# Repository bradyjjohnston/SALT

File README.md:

# 🍞 SALT - Slice And Loaf Telemetry

> A modular home automation and environmental sensing platform, developed in collaboration with **EE4737** and the open-source [BREAD] project.

---

## Overview

BREAD is a modular embedded systems architecture built around a central **Loaf** board and hot-swappable **Slice** modules. Each slice handles its own sensing or control functionality and communicates back to the loaf over a shared protocol (UART). Together, they form a capable at-home weather station and automation hub.

---

## Architecture

```
┌────────────────────────────────────────┐
│              Loaf (Main Board)         │
│   Central controller with female conn. │
│   handles aggregation, data, and logic │
└────────┬────────┬────────┬─────────────┘
         │        │        │
    ┌────┴──┐ ┌───┴──┐ ┌───┴──┐
    │Slice 1│ │Slice2│ │Slice3│  ...
    │SENSE  │ │ ACT. │ │ OPT. │
    └───────┘ └──────┘ └──────┘
```

- **Loaf** — the main board with female connectors, acts as the central hub
- **Slices** — individual modules that plug into the loaf via edge connectors and expose sensor data or control outputs over UART/I2C

---

## Features

- 🌡️ **Environmental monitoring** — temperature, humidity, pressure (BME280)
- 🌐 **Weather data integration** — pulls external weather API data
- 📡 **Modular slice communication** — UART packet protocol between slices and loaf
- 🔌 **Plug-and-play expansion** — add new slices without redesigning the core system
- 🏠 **Home automation ready** — designed to grow into broader automation use cases

---

## Hardware

| Component | Role |
|-----------|------|
| LOAF | facilitates slice data |
| Sense Slice | temp / humidity / pressure sensor / boot sensor |
| Actuation Slice | salt distribution motor control |
| Optics Slice | camera processing and control |
| Power Slice | power outage detection and power distribution |

---

## Communication Protocol

Slices send formatted UART packets to the loaf via DMA when requested by the master MCU. Each packet includes:

- Formatted sensor data

---

## Getting Started

> ⚠️ Hardware required. Software setup instructions coming soon.

1. Clone this repo
2. Open in **STM32CubeIDE**
3. Flash the slice firmware to your Nucleo F303K8
4. Connect the slice to the loaf board via the edge connector
5. Monitor output over UART at `9600` baud and debug over USB at `115200` baud

---

## Project Context

This system was developed as part of **EE4737** coursework and builds on the open-source BREAD framework. The goal is a practical, extensible platform for real-world embedded sensing and home automation experimentation.

---

## License

MIT — see `LICENSE` for details.

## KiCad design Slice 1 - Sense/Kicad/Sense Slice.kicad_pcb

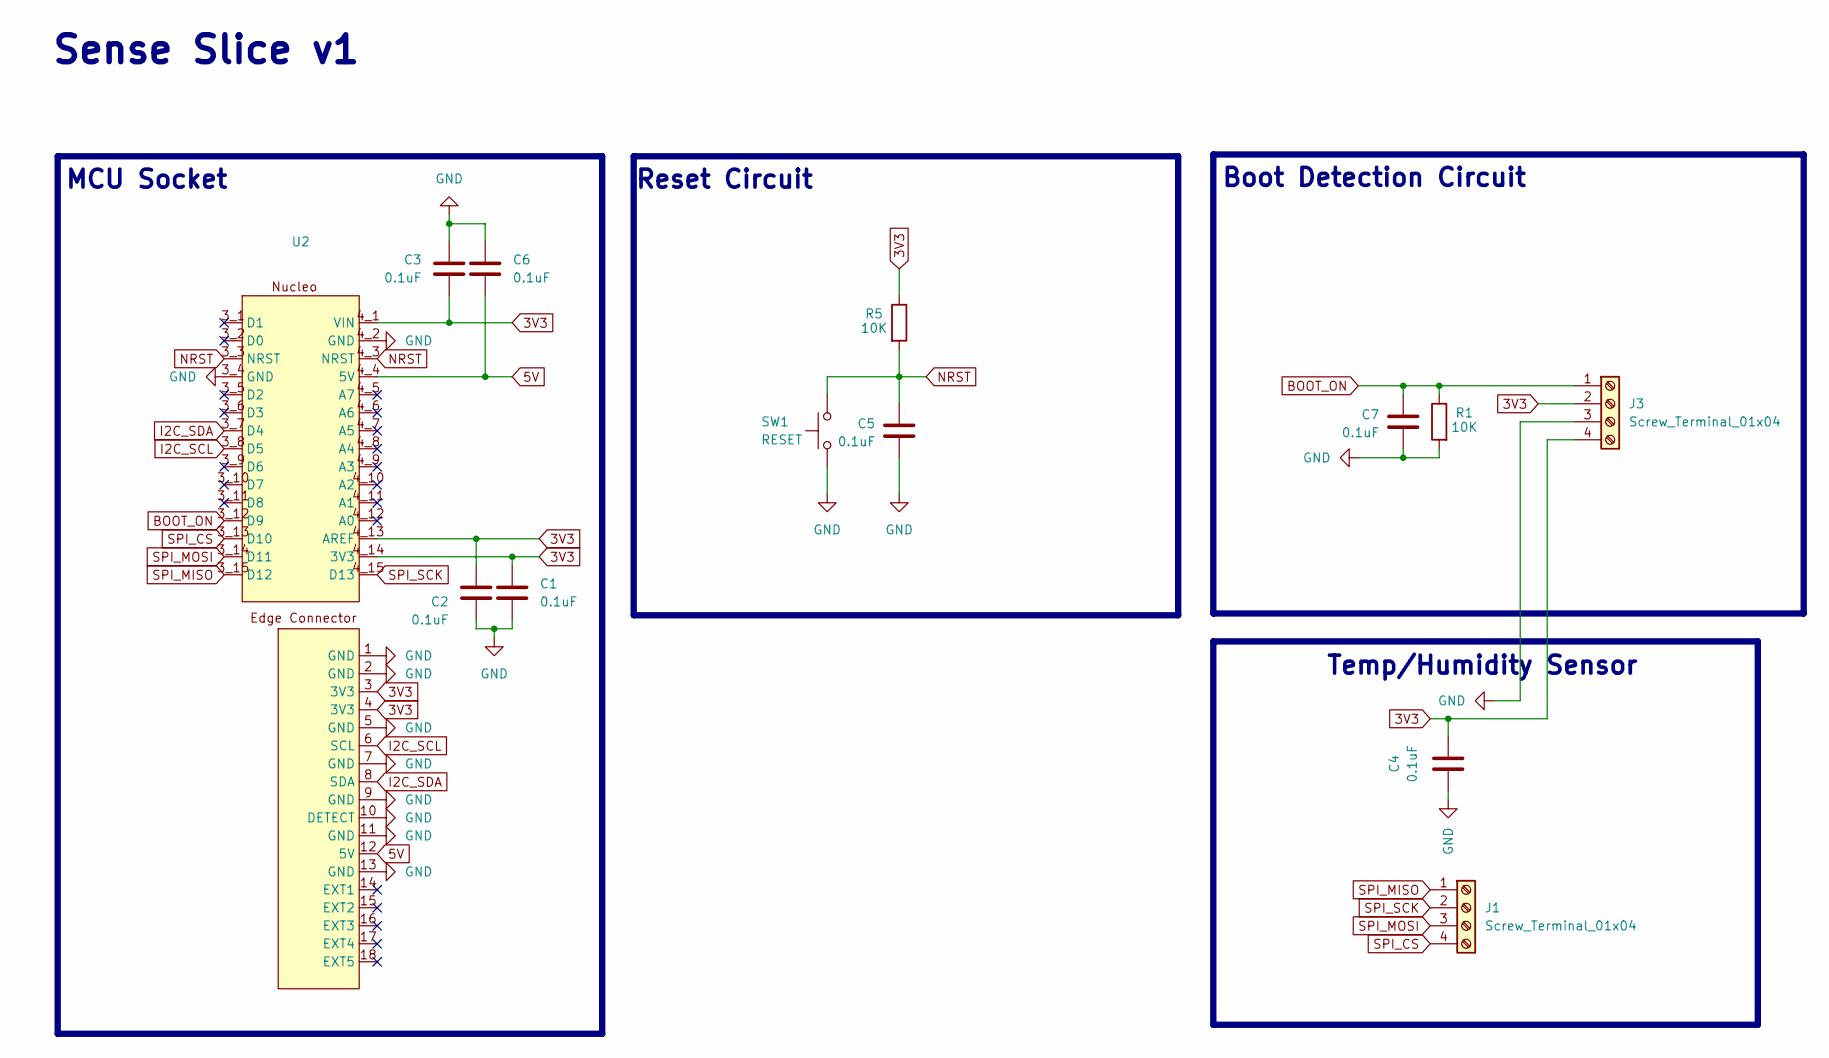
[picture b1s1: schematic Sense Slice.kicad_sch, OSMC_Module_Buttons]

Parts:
C1, C2, C3, C4, C5, C6, C7: 0.1uF; C_0805_2012Metric
J1, J3: Screw_Terminal_01x04; TerminalBlock_MetzConnect_Type011_RT05504HBLC_1x04_P5.00mm_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
R1, R5: 10K; R_0805_2012Metric
SW1: RESET; SW_PUSH_6mm
U2: Team Salt Slice

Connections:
3V3: C1.1, C2.1, C3.2, C4.1, J3.2, J3.4, R5.1, U2.3 (3V3), U2.4 (3V3), U2.4_1 (VIN), U2.4_13 (AREF), U2.4_14 (3V3)
5V: C6.2, U2.4_4 (5V), U2.12 (5V)
BOOT_ON: C7.1, J3.1, R1.1, U2.3_12 (D9)
GND: C1.2, C2.2, C3.1, C4.2, C5.2, C6.1, C7.2, J3.3, R1.2, SW1.1, U2.1 (GND), U2.2 (GND), U2.3_4 (GND), U2.4_2 (GND), U2.5 (GND), U2.7 (GND), U2.9 (GND), U2.10 (DETECT), U2.11 (GND), U2.13 (GND)
I2C_SCL: U2.3_8 (D5), U2.6 (SCL)
I2C_SDA: U2.3_7 (D4), U2.8 (SDA)
NRST: C5.1, R5.2, SW1.2, U2.3_3 (NRST), U2.4_3 (NRST)
SPI_CS: J1.4, U2.3_13 (D10)
SPI_MISO: J1.1, U2.3_15 (D12)
SPI_MOSI: J1.3, U2.3_14 (D11)
SPI_SCK: J1.2, U2.4_15 (D13)

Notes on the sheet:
Temp/Humidity Sensor
Boot Detection Circuit
Sense Slice v1
Reset Circuit
MCU Socket

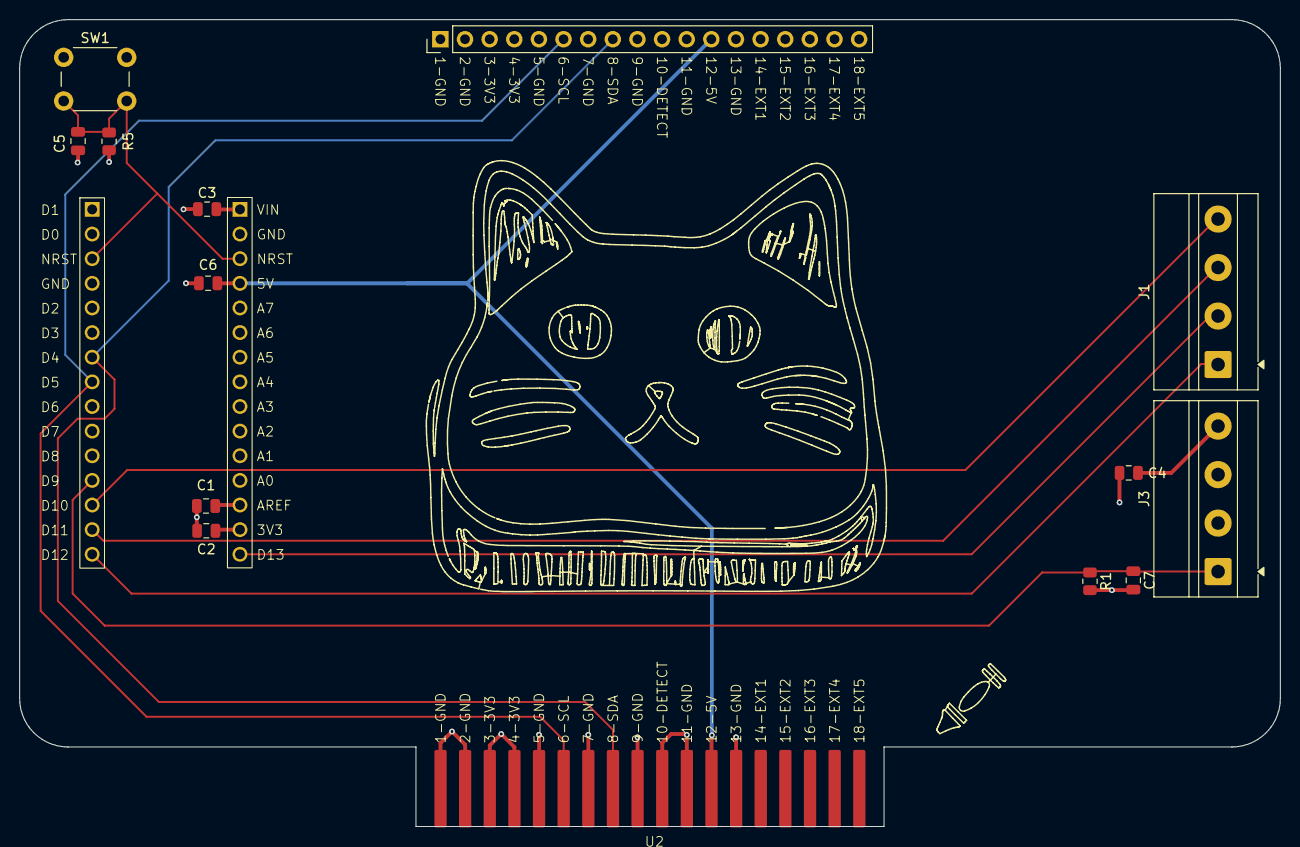
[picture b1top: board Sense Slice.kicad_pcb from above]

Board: 4 copper layers, 130.0 x 83.2 mm, 13 parts (0 on the bottom side), 11 nets.

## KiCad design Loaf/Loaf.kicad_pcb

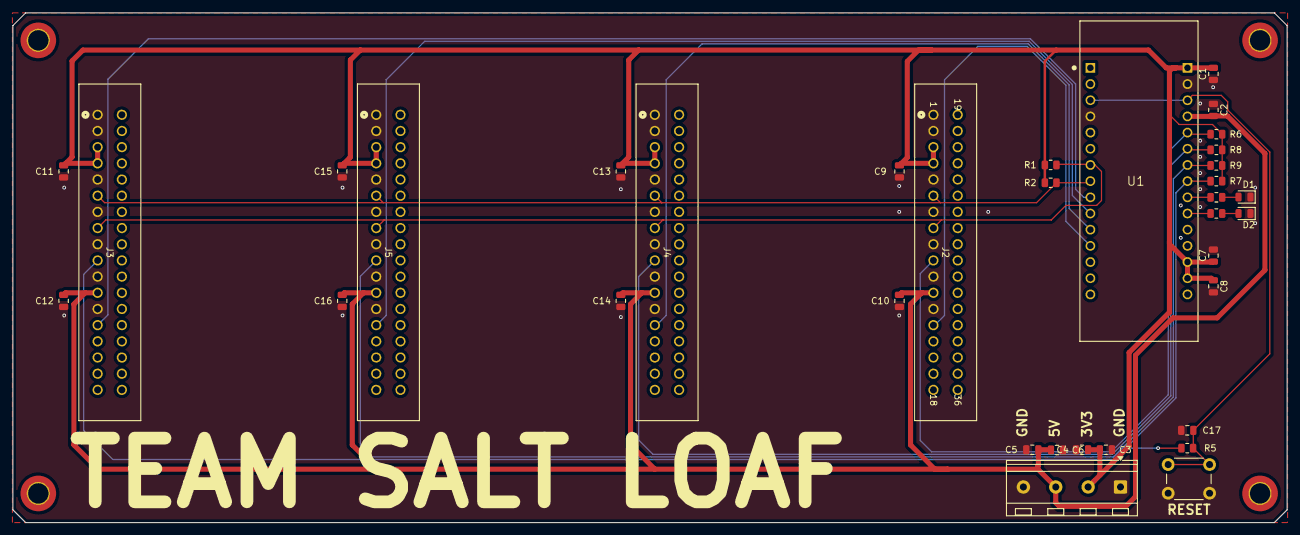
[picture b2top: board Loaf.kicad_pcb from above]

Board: 2 copper layers, 200.0 x 80.0 mm, 35 parts (0 on the bottom side), 18 nets.

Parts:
C1, C2, C7, C8, C17: 0.1uF; C_0805_2012Metric
C3, C4, C5, C6, C9, C10, C11, C12, C13, C14, C15, C16: 10uF; C_0805_2012Metric
D1: USER LED1; LED_0805_2012Metric
D2: USER LED2; LED_0805_2012Metric
J1: Power Input Terminal; TerminalBlock_RND_205-00234_1x04_P5.08mm_Horizontal
J2, J3, J4, J5: 36p Edge Connector; EdgeConnector
R1, R2, R3, R4, R5, R6, R7, R8, R9: 4.7k; R_0805_2012Metric
SW1: BOOT; SW_PUSH_6mm_H5mm
U1: NUCLEO-F303K8; MODULE_NUCLEO-F303K8

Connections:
3V3: C1.2, C3.2, C4.2, C7.1, C8.1, C9.1, C11.1, C13.1, C15.1, J1.2, J2.3, J2.4, J3.3, J3.4, J4.3, J4.4, J5.3, J5.4, R1.2, R2.2, R5.2, R6.1, R7.1, R8.1, R9.1, U1.16 (VIN), U1.28 (AREF), U1.29 (3V3)
5V: C2.2, C5.1, C6.1, C10.1, C12.1, C14.1, C16.1, J1.3, J2.12, J3.12, J4.12, J5.12, U1.19 (5V)
DET_ACT: J5.10, R9.2, U1.22 (A6)
DET_OPT: J3.10, R7.2, U1.23 (A5)
DET_POW: J4.10, R8.2, U1.21 (A7)
DET_SENSE: J2.10, R6.2, U1.20 (A2)
EXT1_ACT: J5.14, U1.10 (F0)
EXT1_OPT: J3.14, U1.9 (B1)
EXT1_POW: J4.14, U1.11 (F1)
EXT1_SENSE: J2.14, U1.12 (A8)
GND: C1.1, C2.1, C3.1, C4.1, C5.2, C6.2, C7.2, C8.2, C9.2, C10.2, C11.2, C12.2, C13.2, C14.2, C15.2, C16.2, C17.2, D1.1 (K), D2.1 (K), J1.1, J1.4, J2.1, J2.2, J2.5, J2.7, J2.9, J2.11, J2.13, J3.1, J3.2, J3.5, J3.7, J3.9, J3.11, J3.13, J4.1, J4.2, J4.5, J4.7, J4.9, J4.11, J4.13, J5.1, J5.2, J5.5, J5.7, J5.9, J5.11, J5.13, SW1.1, U1.4 (GND), U1.17 (GND)
I2C_SCL: J2.6, J3.6, J4.6, J5.6, R2.1, U1.8 (B6)
I2C_SDA: J2.8, J3.8, J4.8, J5.8, R1.1, U1.7 (B7)
NRST: C17.1, R5.1, SW1.2, U1.3 (NRST), U1.18 (NRST)
unnamed: D1.2 (A), R4.2
unnamed: D2.2 (A), R3.2
unnamed: R3.1, U1.25 (A3)
unnamed: R4.1, U1.24 (A4)

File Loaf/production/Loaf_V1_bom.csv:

Designator,Footprint,Quantity,Value,LCSC Part #
"C1, C17, C2, C7, C8",0805,5,0.1uF,
"C10, C11, C12, C13, C14, C15, C16, C3, C4, C5, C6, C9",0805,12,10uF,
D1,0805,1,USER LED1,
D2,0805,1,USER LED2,
J1,TerminalBlock_RND_205-00234_1x04_P5.08mm_Horizontal,1,Power Input Terminal,
"J2, J3, J4, J5",EdgeConnector,4,36p Edge Connector,
"R1, R2, R3, R4, R5, R6, R7, R8, R9",0805,9,4.7k,
SW1,SW_PUSH_6mm_H5mm,1,BOOT,
U1,MODULE_NUCLEO-F303K8,1,NUCLEO-F303K8,

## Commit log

2026-04-21 Revise README for BREAD project details and structure
2026-04-21 Added Folders
